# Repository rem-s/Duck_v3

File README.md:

# Duck_v3 ROS2 tutorial

This is a tutorial for ROS2.

## ***For everyone(必ず読むこと)***
    このドキュメントの参照の仕方
    (h): commands in host computer (your terminal, WSL)
    (c): commands in docker container
    (h/Mac): commands in Mac user
    (h/Windows): commands in Windows user

    なんかしらのエラーが出たらヘルプセクション
    "Section.(Help) ~" を見ること

## 1. Install Docker from the following page
* [Install Docker Desktop on Windows](https://docs.docker.com/docker-for-windows/install/)

* [Install Docker Desktop on Mac](https://docs.docker.com/docker-for-mac/install/)

## 2-1. Run a ROS2 container

1. (Windows) WSL上でROSを動かすフォルダを作成&移動す
る。

2. 以下のリンクに書かれているDockerfileからROS2:dashingのimageをbuildする。
[参考にしてほしいROS2:dashingのDockerfile](https://tshell.hatenablog.com/entry/2020/02/13/174414)

3. Buildが成功したらコンテナを起動し、2-1.1のブログにかいてあるlistener&talkerのプログラムを実行する。

## 2-2. Do the tutorial(ros2:foxy)

1. GUIの環境を整える(以下のHelpを確認すること)
2. [Introducing turtlesim and rqt](https://docs.ros.org/en/foxy/Tutorials/Turtlesim/Introducing-Turtlesim.html) で、turtlesimをやる
3. turtlesimの起動方法
    Xlaunchを起動
    linuxを起動
    linux上で
    　docker ps -a　これでdocker内にあるコンテナがわかる。
    　docker start コンテナID　dockerで作ったコンテナを起動
    　docker exec -it コンテナID /bin/bash　起動したコンテナの中に入る
    　echo $DISPLAY　DISPLAYのアドレスが何に設定されているか見る。
    　export DISPLAY=アドレス　ディスプレイを設定する
　   　このとき、powershell上でipconfigを実行して、Wireless LAN adapter Wi-Fi:Ipv4アドレスを取得。
　   　そのアドレスの末尾に:0.0をつける。
    　ros2 run turtlesim turtlesim_node　最後にこれを実行するとturtlesimが起動する。

## 2-2.1. (Help) Install & run X-server VcXsrv(Windows) or XQuartz(Mac) to enable GUI software
```
ros2 run turtlesim turtlesim_node
```
上記のturtlesimを実行しても何も出てこない場合、このヘルプを見て対処してください。(あくまでも１つの例です。)

これらのリンクを参考にしながら、以下のコマンド(1-4)を実行すること。

- "QStandardPaths: XDG_RUNTIME_DIR not set, defaulting to '/tmp/runtime-root'" みたいなwarningが出たら<br>
    ```
    export XDG_RUNTIME_DIR=/tmp/runtime-root
    ```
- "
qt.qpa.screen: QXcbConnection: Could not connect to display 
Could not connect to any X display." みたいなエラーが出たら<br>
    - [Run GUI app in linux docker container on windows host](https://dev.to/darksmile92/run-gui-app-in-linux-docker-container-on-windows-host-4kde)
    - [【LinuxアプリをWindowsで動かそう】WSLでLinuxのGUIアプリを起動する話](https://veresk.hatenablog.com/entry/2020/02/26/190000)
    - [Docker for Mac で X11 アプリケーションを動かす](https://qiita.com/hoto17296/items/bdb2ab24bc32b6b7f360)
- "libGL error: No matching fbConfigs or visuals found libGL error: failed to load driver: swrast" みたいなエラーが出たら<br>
    - [libGL error: No matching fbConfigs or visuals found libGL error: failed to load driver: swrast #253](https://github.com/jessfraz/dockerfiles/issues/253)<br>
    - [Win10 linux subsystem libGL error: No matching fbConfigs or visuals found libGL error: failed to load driver: swrast](https://askubuntu.com/questions/1127011/win10-linux-subsystem-libgl-error-no-matching-fbconfigs-or-visuals-found-libgl)
    
## For Windows, install & run VcXsrv 
Use __chocolately__ to install VcXsrv.
Then, run Xlaunch and save config file.

For the manual installation, go https://sourceforge.net/projects/vcxsrv/

## For Mac, install & run XQuartz 
For the manual installation, ぐぐって自分で調べる。
- XQuartz をデスクトップから起動
- Xterm が起動することを確認
```
1. (h/Windows) choco install vcxsrv
```

```
2. (h) export DISPLAY=YourHostIP:0.0
ex.) export DISPLAY=192.168.10.0:0.0
```
Check your host ip address with 'ipconfig' command in advance.

```
3. (h) docker run -it -e DISPLAY=$DISPLAY ros2:dashing

(h/Mac) docker run -it -e DISPLAY=$DISPLAY -v ~/.Xauthority:/root/.Xauthority ros2:dashing
```
Create new container named ros2:dashing, passing a environment variable. (You may need to mount .Xauthority file to the docker container, if you are using Mac)

```
4. (c) apt update && apt install -y mesa-utils glxgears
```
Install library allowing us to use GUI features.
(you may need an additional library if you have nvidia driver. Run 'apt install nvidia-340')

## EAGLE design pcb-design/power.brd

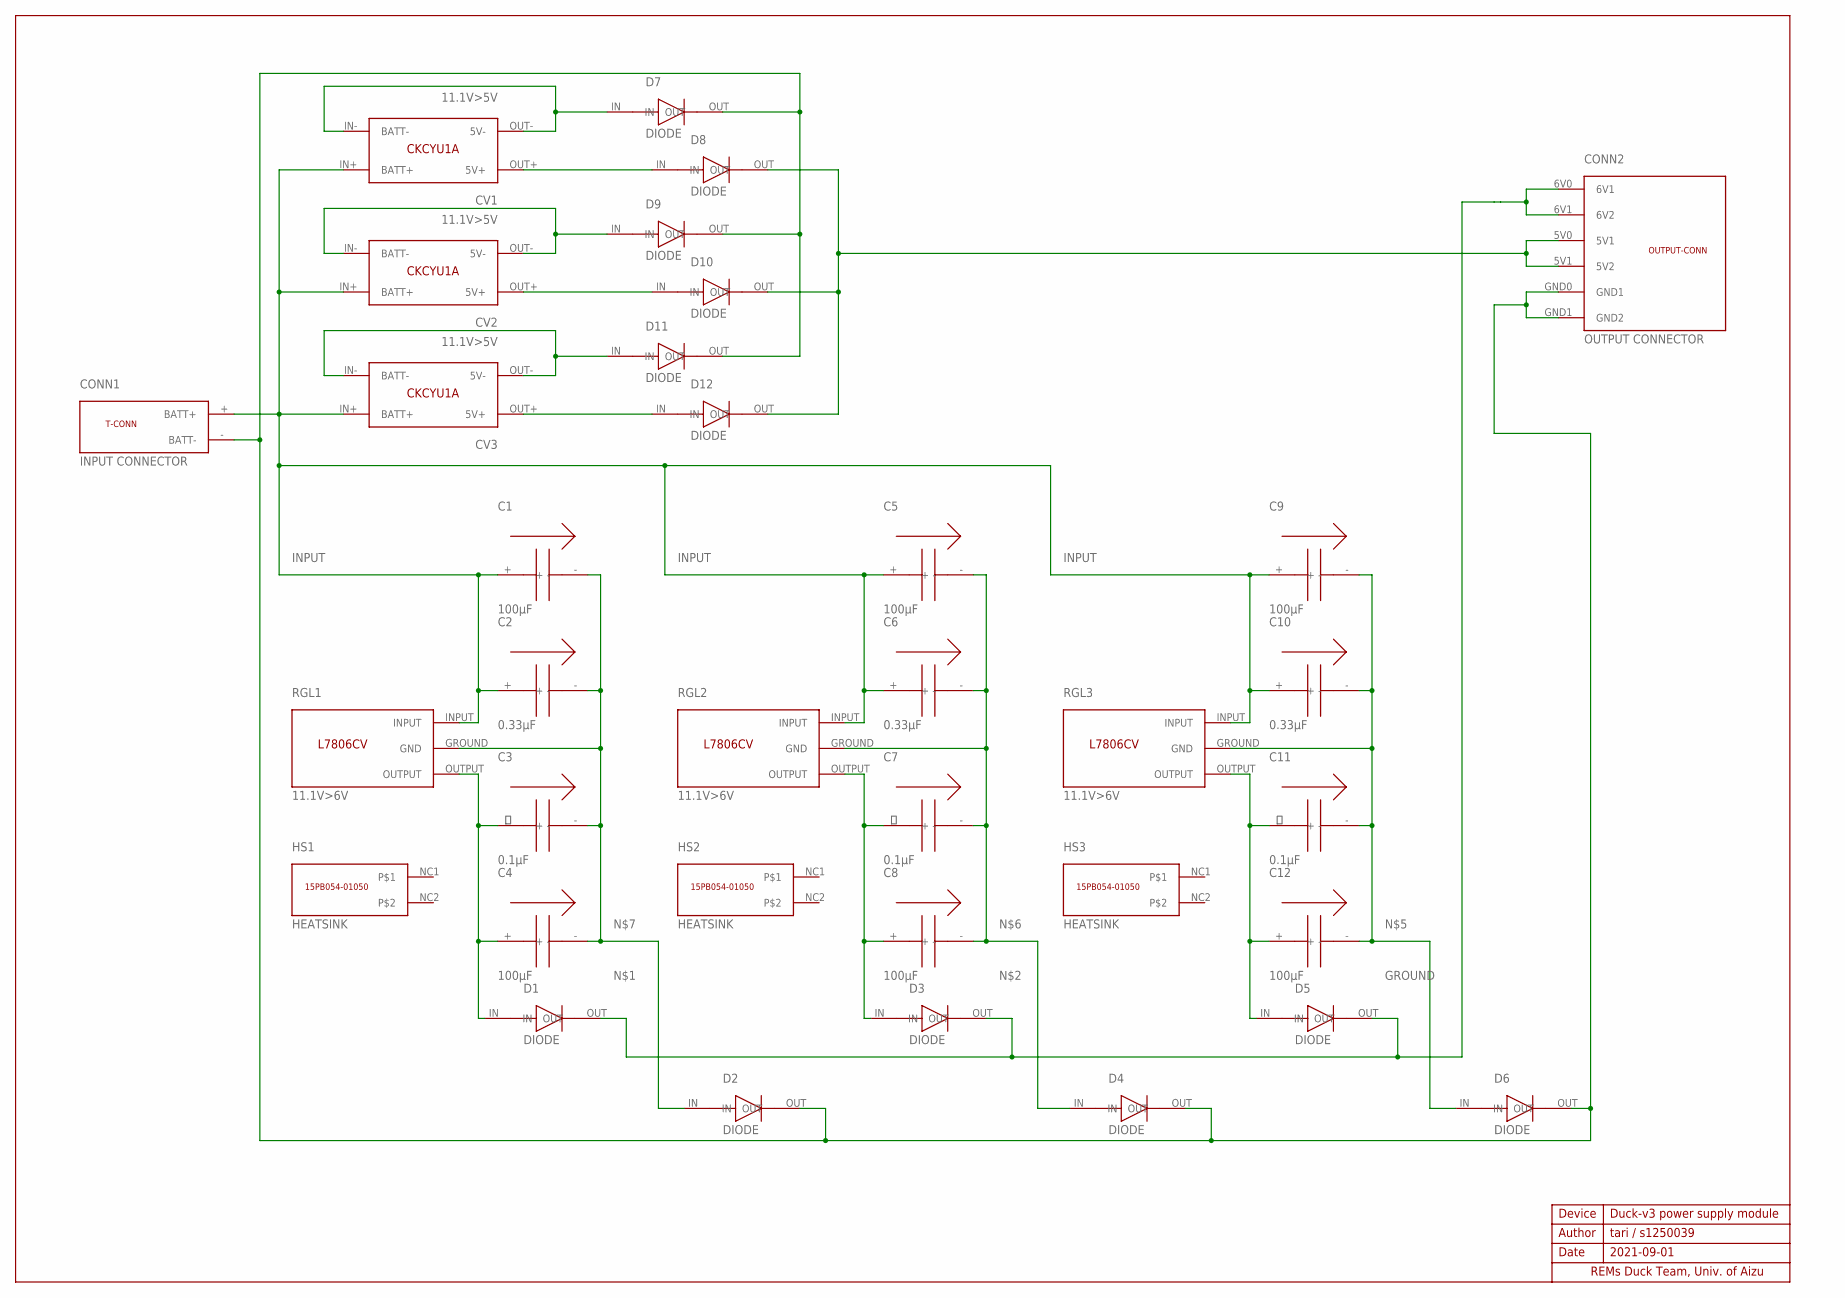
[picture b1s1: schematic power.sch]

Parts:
C1, C4, C5, C8, C9, C12: 100μF; C-100μF
C2, C6, C10: 0.33μF; C-0.33μF
C3, C7, C11: 0.1μF; C-0.1μF
CONN1: INPUT CONNECTOR; T-CONN
CONN2: OUTPUT CONNECTOR; OUTPUT-CONN
CV1, CV2, CV3: 11.1V>5V; CKCYU1A
D1, D2, D3, D4, D5, D6, D7, D8, D9, D10, D11, D12: DIODE
HS1, HS2, HS3: HEATSINK; 15PB054-01050
RGL1, RGL2, RGL3: 11.1V>6V; L7806CV

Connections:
5V: CV3.OUT+ (5V+), D12.IN
GROUND: CONN1.- (BATT-), CONN2.GND0 (GND1), CONN2.GND1 (GND2), D2.OUT, D4.OUT, D6.OUT, D7.OUT, D9.OUT, D11.OUT
INPUT: C1.+, C2.+, C5.+, C6.+, C9.+, C10.+, CONN1.+ (BATT+), CV1.IN+ (BATT+), CV2.IN+ (BATT+), CV3.IN+ (BATT+), RGL1.INPUT, RGL2.INPUT, RGL3.INPUT
unnamed: C3.＋ (+), C4.+, D1.IN, RGL1.OUTPUT
unnamed: C7.＋ (+), C8.+, D3.IN, RGL2.OUTPUT
unnamed: CV3.IN- (BATT-), CV3.OUT- (5V-), D11.IN
unnamed: CONN2.6V0 (6V1), CONN2.6V1 (6V2), D1.OUT, D3.OUT, D5.OUT
unnamed: C9.-, C10.-, C11.-, C12.-, D6.IN, RGL3.GROUND (GND)
unnamed: C5.-, C6.-, C7.-, C8.-, D4.IN, RGL2.GROUND (GND)
unnamed: C1.-, C2.-, C3.-, C4.-, D2.IN, RGL1.GROUND (GND)
unnamed: C11.＋ (+), C12.+, D5.IN, RGL3.OUTPUT
unnamed: CV2.IN- (BATT-), CV2.OUT- (5V-), D9.IN
unnamed: CONN2.5V0 (5V1), CONN2.5V1 (5V2), D8.OUT, D10.OUT, D12.OUT
unnamed: CV1.IN- (BATT-), CV1.OUT- (5V-), D7.IN
unnamed: CV1.OUT+ (5V+), D8.IN
unnamed: CV2.OUT+ (5V+), D10.IN

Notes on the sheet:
Author
Device
Date
REMs Duck Team, Univ. of Aizu
tari / s1250039
2021-09-01
Duck-v3 power supply module

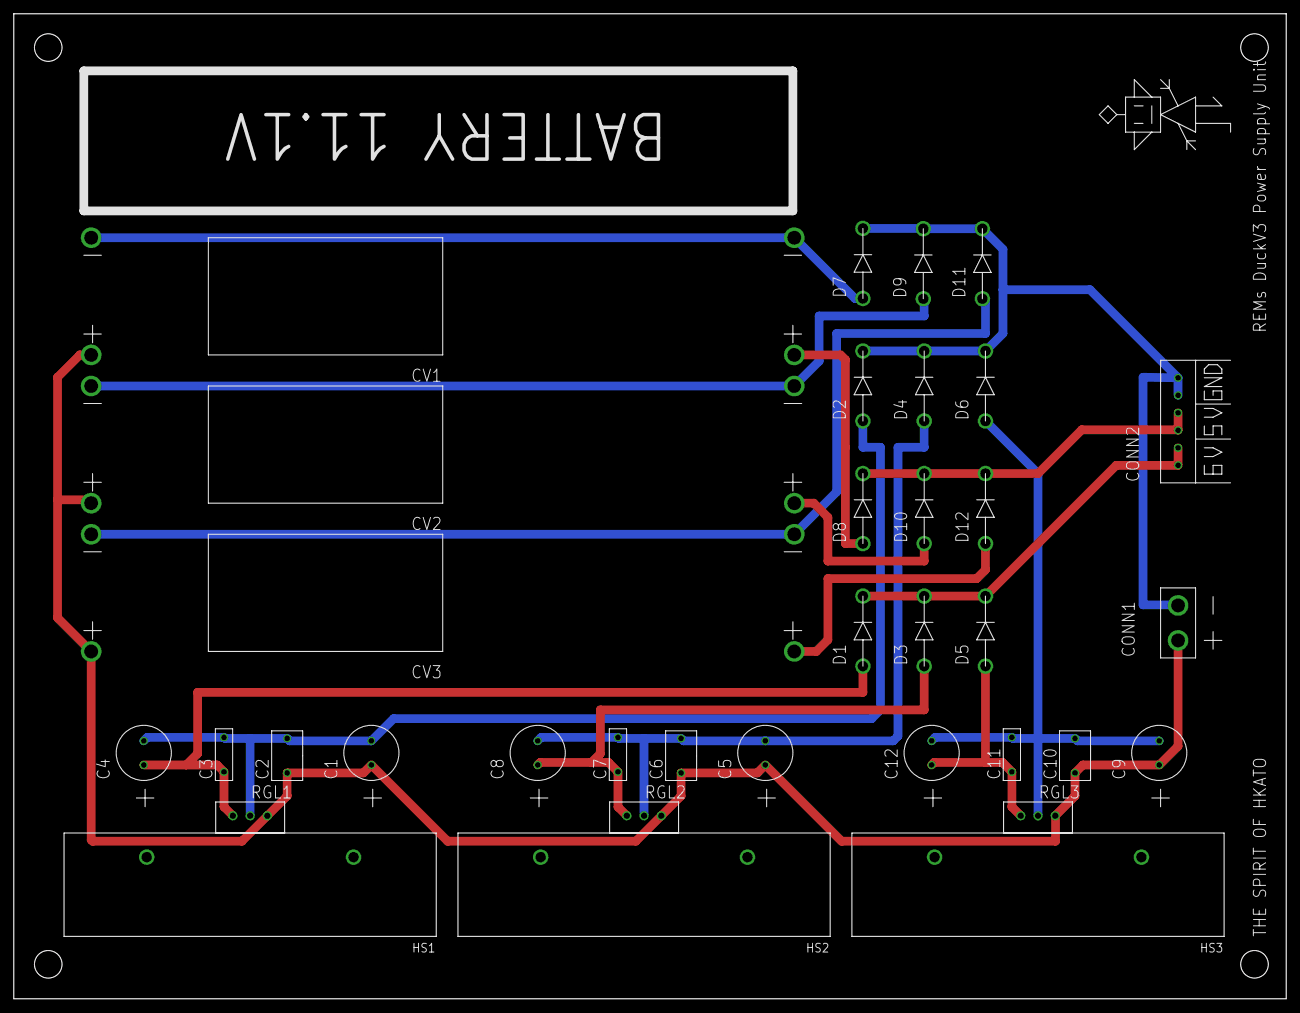
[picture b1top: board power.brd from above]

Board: 2 copper layers, 184.6 x 142.9 mm, 35 parts (0 on the bottom side), 16 nets.

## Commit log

2021-04-07 add readme
2021-04-07 add some changes
2021-04-08 add comments
2021-05-30 modified readme
2021-06-06 add docker-compose
2021-06-06 mistake
2021-06-27 update docker-compose
2021-06-27 modified dockerfile
2021-07-04 modified docker-compose
2021-08-18 initialize
2021-08-26 wait for order parts
2021-08-29 add duck_sensor and duck_navigation
2021-08-29 Remove ignored files
2021-08-29 Add footprint
2021-08-29 removed ignored file
2021-09-01 change directory
2021-09-01 modify library
2021-09-01 board create
2021-09-02 finished board
2021-09-08 wide battery place
2021-09-09 Before dinner
2021-09-10 before lunch
2021-09-10 before sleep
2021-09-16 Update board
2021-09-17 before go out
2021-09-20 correct err
2021-10-24 diode update
2021-10-26 FINAL
    FINAL
2022-08-16 duck operator_ws/machine_wsの追加
2022-08-16 test
2022-08-17 add requirements.txt
2022-08-18 add child programs
2022-08-19 set device type to cpu
2022-08-21 test pid
2022-08-28 modified detect.py and add model.pt
2022-08-31 デバッグ
    一か所穴があいていなかった
2022-08-31 mechanum ctl by color detection
